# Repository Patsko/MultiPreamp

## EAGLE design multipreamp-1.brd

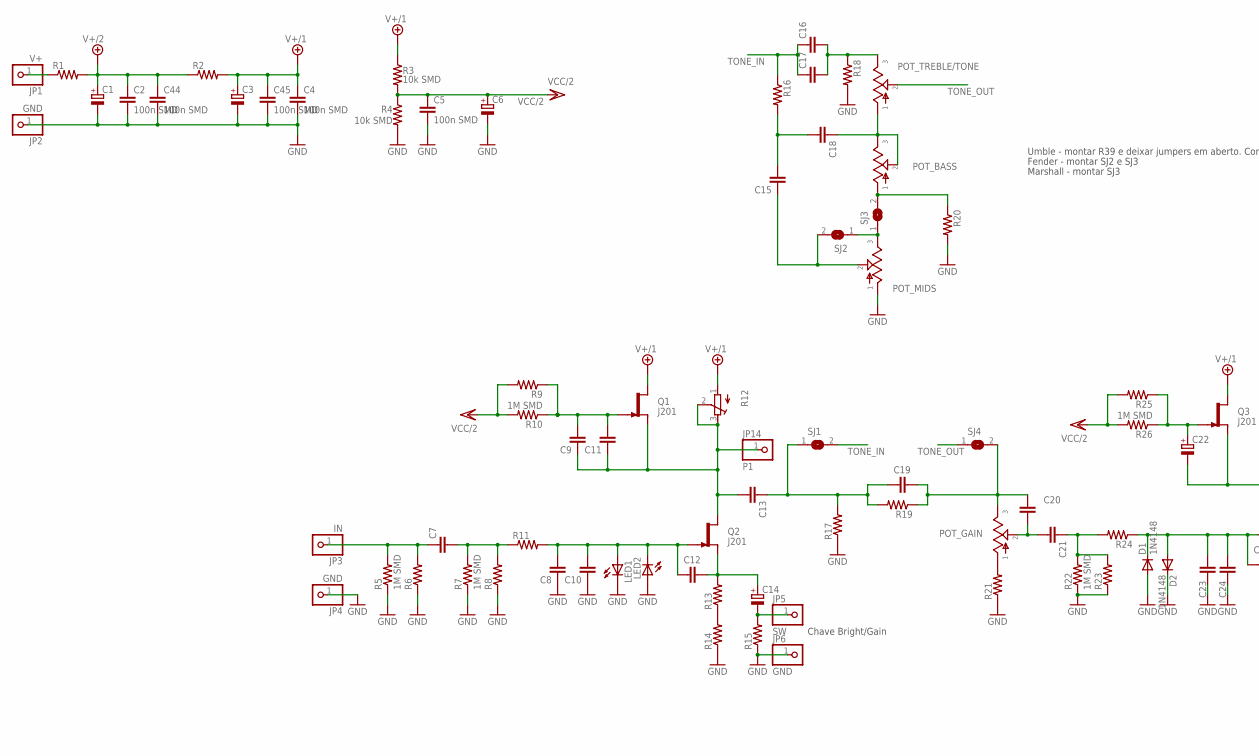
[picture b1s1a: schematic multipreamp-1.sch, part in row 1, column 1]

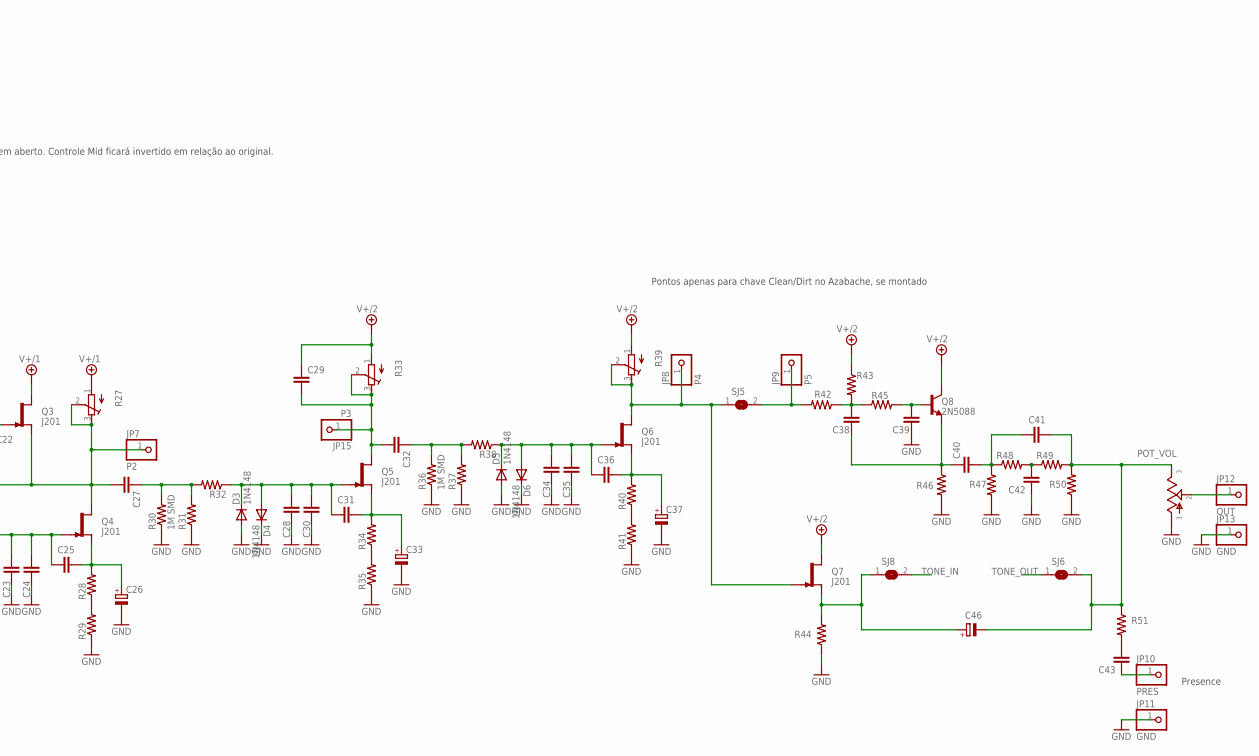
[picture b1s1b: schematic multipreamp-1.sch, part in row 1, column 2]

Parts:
C1, C3, C6, C14, C22, C26, C33, C37, C46: CPOL-EUE2.5-6; E2,5-6
C2, C4, C5, C44, C45: 100n SMD; C0805
C7, C13, C15, C18, C19, C21, C27, C29, C32, C38, C40, C41, C42, C43: C-EU050-025X075; C050-025X075
C8, C9, C10, C11, C12, C16, C17, C20, C23, C24, C25, C28, C30, C31, C34, C35, C36, C39: C-EU025-025X050; C025-025X050
D1, D2, D3, D4, D5, D6: 1N4148; DO35-7
JP1: V+; 1X01
JP2, JP4, JP6, JP11, JP13: GND; 1X01
JP3: IN; 1X01
JP5: SW; 1X01
JP7: P2; 1X01
JP8: P4; 1X01
JP9: P5; 1X01
JP10: PRES; 1X01
JP12: OUT; 1X01
JP14: P1; 1X01
JP15: P3; 1X01
LED1, LED2: LED3MM
POT_BASS: POTPCB; 16MM-PCB-MOUNT
POT_GAIN: POTPCB; 16MM-PCB-MOUNT
POT_MIDS: POTPCB; 16MM-PCB-MOUNT
POT_TREBLE/TONE: POTPCB; 16MM-PCB-MOUNT
POT_VOL: POTPCB; 16MM-PCB-MOUNT
Q1, Q2, Q3, Q4, Q5, Q6, Q7: J201; TO92-
Q8: 2N5088; TO92-
R1, R2, R11, R13, R14, R15, R16, R17, R18, R19, R20, R23, R24, R28, R29, R31, R32, R34, R35, R37, R38, R40, R41, R42, R43, R44, R45, R46, R47, R48, R49, R50, R51: R-US_0207/7; 0207/7
R3, R4: 10k SMD; R0805
R5, R7, R10, R22, R26, R30, R36: 1M SMD; R0805
R6, R8: R-US_0207/2V; 0207/2V
R9, R25: R-US_0207/5V; 0207/5V
R12, R27, R33, R39: R-TRIMM3296W; RTRIM3296W
R21: R-US_R0805; R0805
SJ1, SJ2, SJ3, SJ4, SJ5, SJ6, SJ8: SJ

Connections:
GND: C1.-, C2.2, C3.-, C4.2, C5.2, C6.-, C8.1, C10.1, C23.1, C24.1, C26.-, C28.1, C30.1, C33.-, C34.1, C35.1, C37.-, C39.1, C42.1, C44.2, C45.2, D1.A, D2.C, D3.A, D4.C, D5.A, D6.C, JP2.1, JP4.1, JP6.1, JP11.1, JP13.1, LED1.K (C), LED2.A, POT_MIDS.1, POT_VOL.1, R4.2, R5.1, R6.1, R7.1, R8.1, R14.1, R15.1, R17.1, R18.2, R20.2, R21.1, R22.1, R23.1, R29.1, R30.1, R31.1, R35.1, R36.1, R37.1, R41.1, R44.1, R46.2, R47.2, R50.1
unnamed: C14.-, JP5.1, R15.2
unnamed: C12.1, C14.+, Q2.2 (S), R13.2
unnamed: C20.1, C21.2, POT_GAIN.2
unnamed: C8.2, C10.2, C12.2, LED1.A, LED2.K (C), Q2.1 (G), R11.2
unnamed: C7.2, R7.2, R8.2, R11.1
unnamed: C15.1, POT_MIDS.2, SJ2.2
unnamed: C9.2, C11.2, Q1.1 (G), R9.1, R10.1
unnamed: C9.1, C11.1, C13.2, JP14.1, Q1.2 (S), Q2.3 (D), R12.2 (S), R12.3 (E)
unnamed: C41.2, C46.-, POT_VOL.3, R49.2, R50.2, R51.1, SJ6.2
unnamed: C43.2, R51.2
unnamed: C19.1, C20.2, POT_GAIN.3, R19.1, SJ4.2
unnamed: POT_GAIN.1, R21.2
unnamed: C21.1, R22.2, R23.2, R24.2
unnamed: C43.1, JP10.1
unnamed: C22.-, C27.2, JP7.1, Q3.2 (S), Q4.3 (D), R27.2 (S), R27.3 (E)
unnamed: C25.1, C26.+, Q4.2 (S), R28.2
unnamed: R28.1, R29.2
unnamed: C27.1, R30.2, R31.2, R32.2
unnamed: C28.2, C30.2, C31.2, D3.C, D4.A, Q5.1 (G), R32.1
unnamed: C31.1, C33.+, Q5.2 (S), R34.2
unnamed: R34.1, R35.2
unnamed: C29.2, C32.2, JP15.1, Q5.3 (D), R33.2 (S), R33.3 (E)
unnamed: C38.1, R42.1, R43.2, R45.1
unnamed: C32.1, R36.2, R37.2, R38.2
unnamed: C34.2, C35.2, C36.2, D5.C, D6.A, Q6.1 (G), R38.1
unnamed: C36.1, C37.+, Q6.2 (S), R40.2
unnamed: R40.1, R41.2
unnamed: JP8.1, Q6.3 (D), Q7.1 (G), R39.2 (S), R39.3 (E), SJ5.1
unnamed: JP9.1, R42.2, SJ5.2
unnamed: C39.2, Q8.2 (B), R45.2
unnamed: C38.2, C40.1, Q8.3 (E), R46.1
unnamed: C40.2, C41.1, R47.1, R48.1
unnamed: C42.2, R48.2, R49.1
unnamed: R13.1, R14.2
unnamed: JP12.1, POT_VOL.2
unnamed: C15.2, C18.2, R16.2
unnamed: POT_MIDS.3, SJ2.1, SJ3.1
unnamed: C7.1, JP3.1, R5.2, R6.2
unnamed: C13.1, C19.2, R17.2, R19.2, SJ1.1
unnamed: C22.+, Q3.1 (G), R25.1, R26.1
unnamed: C23.2, C24.2, C25.2, D1.C, D2.A, Q4.1 (G), R24.1
unnamed: POT_BASS.1, R20.1, SJ3.2
unnamed: JP1.1, R1.1
unnamed: C46.+, Q7.2 (S), R44.2, SJ8.1
TONE/TREBLE_1: C18.1, POT_BASS.2, POT_BASS.3, POT_TREBLE/TONE.1
TONE/TREBLE_3: C16.2, C17.2, POT_TREBLE/TONE.3, R18.1
TONE_IN: C16.1, C17.1, R16.1, SJ1.2, SJ8.2
TONE_OUT: POT_TREBLE/TONE.2, SJ4.1, SJ6.1
V+/1: C3.+, C4.1, C45.1, Q1.3 (D), Q3.3 (D), R2.2, R3.1, R12.1 (A), R27.1 (A)
V+/2: C1.+, C2.1, C29.1, C44.1, Q7.3 (D), Q8.1 (C), R1.2, R2.1, R33.1 (A), R39.1 (A), R43.1
VCC/2: C5.1, C6.+, R3.2, R4.1, R9.2, R10.2, R25.2, R26.2

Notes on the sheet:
Umble - montar R39 e deixar jumpers em aberto. Controle Mid ficará invertido em relação ao original.
Marshall - montar SJ3
Pontos apenas para chave Clean/Dirt no Azabache, se montado
Chave Bright/Gain
Presence
Fender - montar SJ2 e SJ3

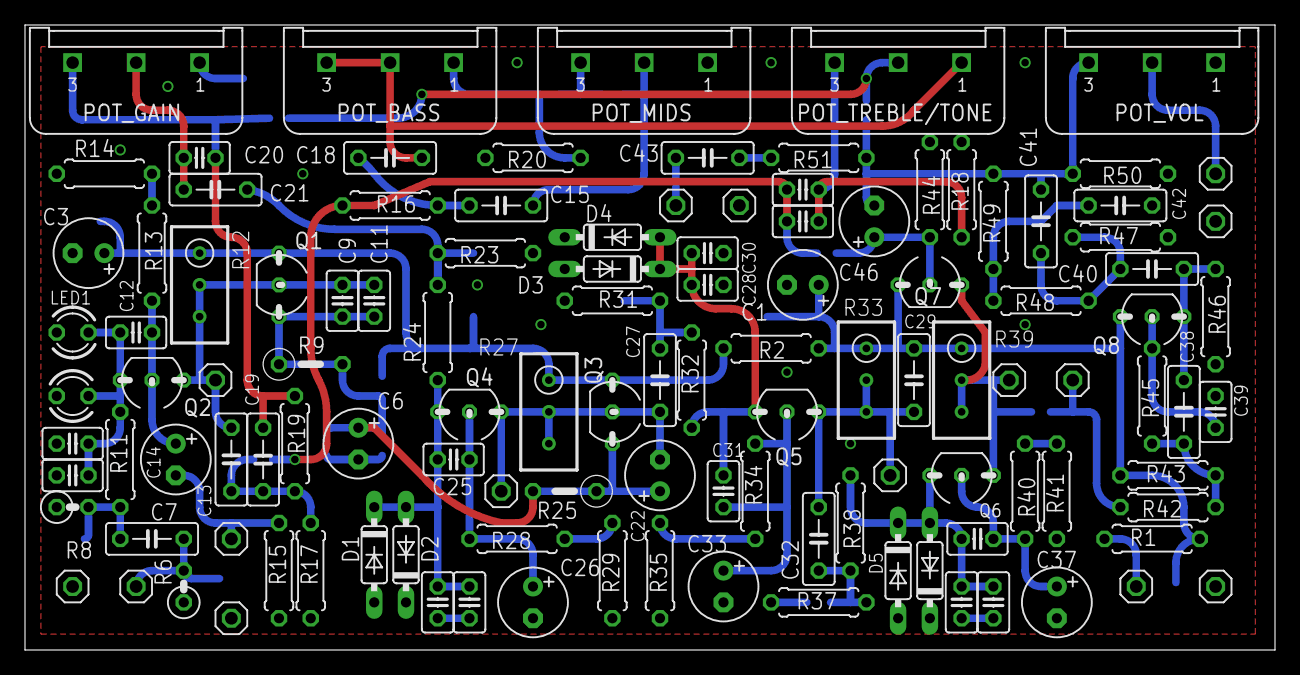
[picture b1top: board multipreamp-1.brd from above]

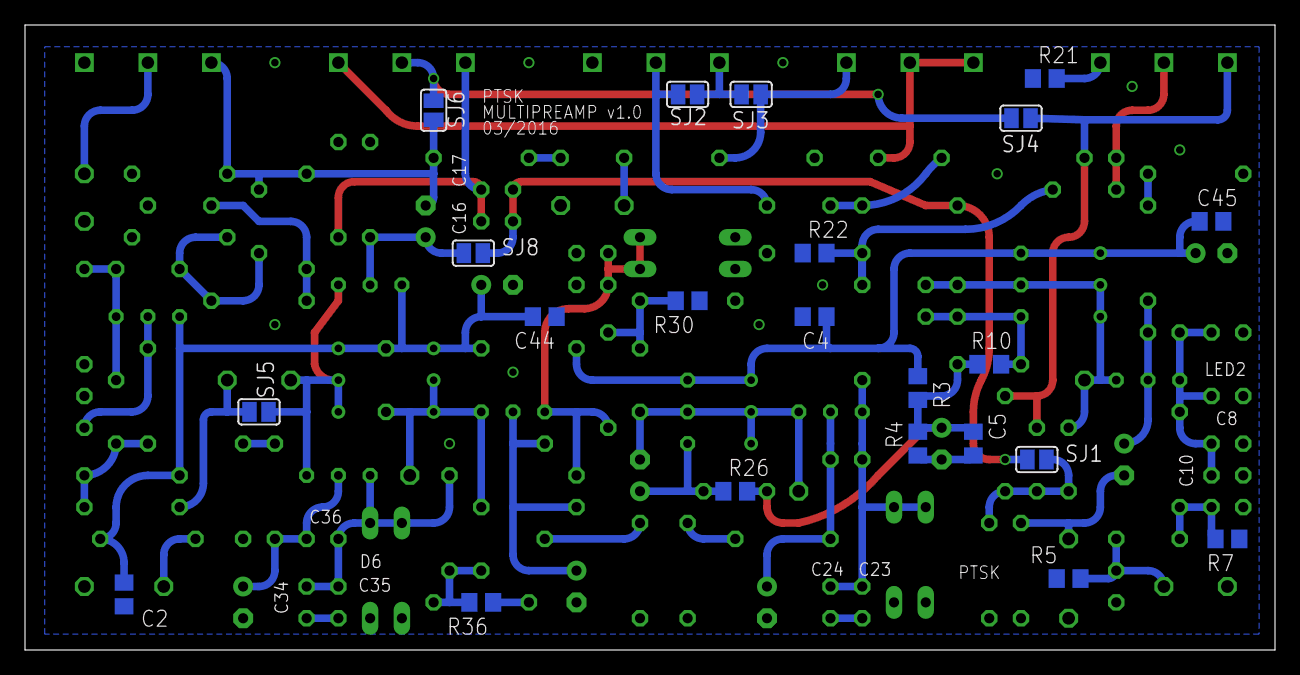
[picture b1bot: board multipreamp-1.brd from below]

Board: 2 copper layers, 100.0 x 50.0 mm, 140 parts (22 on the bottom side), 52 nets.

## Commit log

2015-04-27 Commit inicial
2015-05-02 Desenvolvimento do esquematico
2015-07-01 Ajustes no esquematico e no layout
2016-01-30 Desenvolvimento do layout - roteamento da placa Pendente roteamento do terra e análises do esquematico e layout
2016-02-07 Revisao do esquematico
2016-02-08 Alteracoes e correcoes no esquematico e layout apos verificacao para montagem de Azabache/Spitfire/Dr Boogie
2016-02-08 Ajustes no tonestack para contemplar montagens Fender/Marshall/Dumble
2016-02-10 Adicao de filtros RC na alimentacao (esquematico e layout)
2016-02-14 Alteracao no layout - troca de posicao entre pots de agudos e graves
2016-02-14 Alteracoes no layout - troca de encapsulamentos Renumeracao dos componentes
2016-02-22 Alteracao no esquematico e layout - adicao de jumper para selecao da ligacao na saida do buffer JFET
2016-03-04 Ajustes no layout - troca de encapsulamento dos trimpots
2016-03-04 Ajustes no esquematico e adicao de capacitores de bypass
2016-03-19 Ajustes no layout e criacao do plano de terra DRC executado, sem erros
2016-03-20 Troca do potenciometro por modelo com layers corretos para silkagem na PCB Ajustes no layout
2016-03-22 Ajustes no esquematico e layout - Adicao de capacitor em serie com buffer FET de saida, ajuste de posicionamento de labels, adicao de vias
2016-03-24 Ajustes finais no layout e esquematico - posicionamento de labels, troca de testpoints por pinheads, adicao de assinatura na placa Gerber v1.0 gerado com base nessa versao
